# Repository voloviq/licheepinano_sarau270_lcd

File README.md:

# licheepinano_sarau270_lcd
LicheePi Nano Sara U270 Development Board

3D View of Board

PCB footprint is desinged for R19-2 SCI package

https://www.tme.eu/pl/details/absp-19/obudowy-uniwersalne/sci/r19-2/

### Limitation

GSM antenna is not well designed. In this pcb footprint it can be difficult or impossible to do it well. To achieve maximum performance use SMD connector with external antenna.

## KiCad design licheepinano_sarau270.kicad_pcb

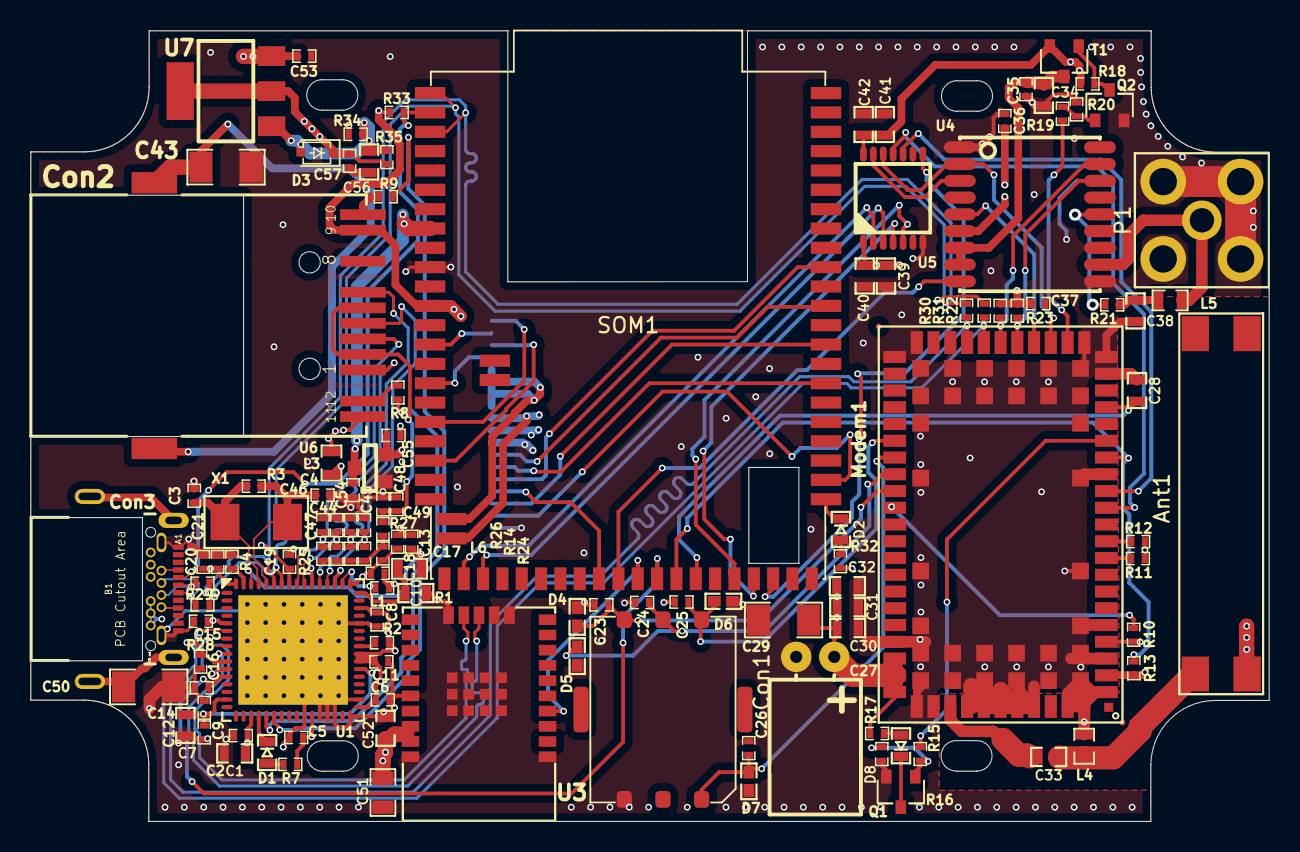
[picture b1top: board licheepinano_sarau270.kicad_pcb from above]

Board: 4 copper layers, 81.3 x 51.9 mm, 120 parts (1 on the bottom side), 92 nets.

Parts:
Ant1: MEE04
C1, C7: 4.7uF/6V3; 4_7uF_0603
C2, C5, C6, C8, C9, C11, C12, C13, C14, C15, C16, C17, C18, C19, C20, C21, C35, C36, C37: 100nF/50V; 100nF_0402
C3, C4: 30pF/50V; 30pF_0402
C10, C34, C38, C39, C41: 1uF/6V3; 1uF_0603
C23, C24, C25, C26: 47pF/50V; 47pF_0402
C27: 220uF/6V3; 220uF_6_3V_Polymer_Horizontal_fi8_len8mm
C28, C30, C31, C32, C40, C42: 100nF/50V; 100nF_0603
C29: 47uF/6V3; 47uF_1206
C33: 10pF; 10pF_0603
C43, C50: 1nF/2kV; 1nF_2kV_1206
C44, C45, C46, C47: 15pF/50V; 15pF_0402
C48, C49: 22nF/25V; 22nF_0402
C51: 10uF/16V; 10uF_0805
C52: 100nF/16V; 100nF_0603
C53, C54, C55, C57: 1uF/10V; 1uF_0402
C56: 10uF/10V; 10uF_10V_0603
Con1: SIM8050-6-0-14-01-A
Con2: WE-RJ45_7498011122AR
Con3: USB_C_Wurth_632723130112; USB_C_632723130112
D1, D2, D8: KPG-1608SURKC-T; LED_KPG-1608SURKC-T
D3: NSR0530H-D; NSR0530H-D_SOD323
D4, D5, D6, D7: PESD0402-140
DIS1: LiangHaoCai_Ili9341_spi
L1, L3: LCBA-601
L4, L5: 39nH; 39nH_0603
L6: BLM15HG601SN1D; BLM15HG601SN1D_0402
Modem1: Sara_U270
P1: RF2-03E-T-00-50-G
Q1, Q2: BC847B; BC847B_SOT23
R1: 12k/1%; 12k4_0402
R2, R10, R11, R12, R15, R19: 10k; 10k_0402
R3: 1M; 1M_0402
R4: 12k/1%; 12k_0402
R7, R8, R9, R17, R32: 470R; 470R_0402
R13, R18: 100k; 100k_0402
R14, R24, R25, R26: 49R9/1%; 49R9_0402
R16, R20, R33: 47k; 47k_0402
R21, R27: 10R; 10R_0402
R22, R23: 2k7; 2k7_0402
R28, R29, R30, R31: 0R; 0R_0402
R34: 1k5; 1k5_0402
R35: 3k3; 3k3_0402
SOM1: LicheePiNano
T1: FDN304P; FDN304P_SOT23
U1: LAN9514I
U3: LILY-W132; LILY_W132
U4: MAX-M8C; Max-M8C
U5: TXB0104; TXB0104_TSSOP14
U6: AP2127K-2.8TRG1; AP2127K-2.8TRG1_SOT23
U7: LM317DCYR; LM317DCYR_SOT223
X1: ABM3-25.000MHZ-D2Y-T

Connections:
3V3: C1.1, C2.1, C5.1, C6.1, C8.1, C11.1, C39.1, C40.1, C51.1, C52.1, Con2.9, Con2.11, L3.2, R2.2, R7.1, R32.1, R33.1, SOM1.53, U1.11, U1.19, U1.27, U1.33, U1.39, U1.40, U1.46, U3.8, U3.9, U5.1
/Ethernet Connector Module/LED_Green_-: Con2.12, R8.1
/Ethernet Connector Module/LED_Yellow_-: Con2.10, R9.1
/Ethernet Connector Module/POWER_IN_3V3: C15.1, C16.1, C17.1, C18.1, C19.1, C20.1, C21.1, L3.1, L6.1, U1.5, U1.10, U1.49, U1.51, U1.54, U1.57, U1.64
/Ethernet Connector Module/SHIELD1: C43.1, Con2.Z1, Con2.Z2
/GPS Module/1V8: C37.1, R22.2, R23.2
/GPS Module/GNSS_ENABLE: Modem1.23, R19.2
/GPS Module/GPS_EXTINT: Modem1.25, U4.5
/GPS Module/GPS_V_BCKP: C36.1, Modem1.2, R13.1, U4.6
/GPS Module/POWER_IN_1V8: C41.1, C42.1, Modem1.4, R10.2, R18.2, T1.S, U5.14
/LCD Module/CLK: DIS1.3, SOM1.14
/LCD Module/CS: DIS1.5, SOM1.10
/LCD Module/DC: DIS1.4, SOM1.34
/LCD Module/LED_A: DIS1.10, SOM1.65
/LCD Module/LED_K1: DIS1.11, DIS1.12, DIS1.13, DIS1.14, SOM1.66
/LCD Module/MISO: DIS1.7, SOM1.12
/LCD Module/MOSI: DIS1.6, SOM1.16
/LCD Module/POWER_IN_2V8: C55.1, DIS1.9, U6.2
/LicheePi Nano SOM/GPIO_PD0: Modem1.15, R13.2, SOM1.30
/LicheePi Nano SOM/GPIO_PD1: C28.1, Modem1.18, SOM1.29
/LicheePi Nano SOM/GPIO_PD5: SOM1.25, U5.8
/LicheePi Nano SOM/GPIO_PD9: SOM1.33, U4.9
/LicheePi Nano SOM/GPIO_PD11: C14.1, SOM1.31, U1.12
/LicheePi Nano SOM/GPIO_PD19: DIS1.2, SOM1.21
/LicheePi Nano SOM/POWER_IN_5V0: C53.1, C54.1, Con3.A4, Con3.A9, Con3.B4, Con3.B9, SOM1.57, U6.3, U7.3
/LicheePi Nano SOM/TPX1: DIS1.17, SOM1.51
/LicheePi Nano SOM/TPX2: DIS1.15, SOM1.49
/LicheePi Nano SOM/TPY1: DIS1.18, SOM1.47
/LicheePi Nano SOM/TPY2: DIS1.16, SOM1.45
/LicheePi Nano SOM/USB_D_N: R28.1, R31.2, SOM1.64, U1.58
/LicheePi Nano SOM/USB_D_P: R29.1, R30.2, SOM1.62, U1.59
/LicheePi Nano SOM/USB_ID: Con3.A5, Con3.B2, Con3.B3, Con3.B5, R33.2, SOM1.63
/Logic Voltage Shifter/SIG1_HIGH_PART: SOM1.41, U5.2
/Logic Voltage Shifter/SIG1_LOW_PART: U4.3, U5.13
/Logic Voltage Shifter/SIG2_HIGH_PART: SOM1.40, U5.3
/Logic Voltage Shifter/SIG2_LOW_PART: Modem1.24, U4.2, U5.12
/Logic Voltage Shifter/SIG3_HIGH_PART: SOM1.26, U5.4
/Logic Voltage Shifter/SIG3_LOW_PART: Modem1.12, U5.11
/Logic Voltage Shifter/SIG4_HIGH_PART: SOM1.27, U5.5
/Logic Voltage Shifter/SIG4_LOW_PART: Modem1.13, U5.10
/Modem 3G/GPS_I2C_1V8_SCL: Modem1.27, R22.1, U4.17
/Modem 3G/GPS_I2C_1V8_SDA: Modem1.26, R23.1, U4.16
/Modem 3G/MODEM_POWER_IN: C27.1, C29.1, C30.1, C31.1, C32.1, C57.1, D3.1, Modem1.51, Modem1.52, Modem1.53, R17.1, R35.1, U7.2, U7.4
/Modem 3G/SIM_CLK: C25.2, Con1.C3, D6.1, Modem1.38
/Modem 3G/SIM_DET: Modem1.42, R10.1
/Modem 3G/SIM_IO: C26.2, Con1.C7, D7.1, Modem1.39
/Modem 3G/SIM_RST: C24.2, Con1.C2, D5.1, Modem1.40
/Modem 3G/VSIM: C23.2, Con1.C1, D4.1, Modem1.41
/UBlox WiFi Lily W132/ENABLE: SOM1.32, U3.14
/USB Hub Module/ETHERNET_RXN: C44.1, Con2.6, R14.2, U1.53
/USB Hub Module/ETHERNET_RXP: C45.1, Con2.4, R24.2, U1.52
/USB Hub Module/ETHERNET_TXN: C46.1, Con2.3, R25.2, U1.56
/USB Hub Module/ETHERNET_TXP: C47.1, Con2.1, R26.2, U1.55
/USB Hub Module/USB_D4_OUT_N: Modem1.28, R31.1, U1.6
/USB Hub Module/USB_D4_OUT_P: Modem1.29, R30.1, U1.7
/USB Hub Module/USB_D5_OUT_N: U1.8, U3.24
/USB Hub Module/USB_D5_OUT_P: U1.9, U3.23
GND: Ant1.0, C1.2, C2.2, C3.2, C4.1, C5.2, C6.2, C7.2, C8.2, C9.2, C10.2, C11.2, C12.2, C13.2, C14.2, C15.2, C16.2, C17.2, C18.2, C19.2, C20.2, C21.2, C23.1, C24.1, C25.1, C26.1, C27.2, C28.2, C29.2, C30.2, C31.2, C32.2, C34.2, C35.2, C36.2, C37.2, C38.2, C39.2, C40.2, C41.2, C42.2, C43.2, C44.2, C45.2, C46.2, C47.2, C48.2, C49.2, C50.2, C51.2, C52.2, C53.2, C54.2, C55.2, C56.2, C57.2, Con1.C5, Con3.A1, Con3.A12, Con3.B1, Con3.B12, D4.2, D5.2, D6.2, D7.2, DIS1.1, DIS1.8, L4.2, Modem1.1, Modem1.3, Modem1.5, Modem1.14, Modem1.20, Modem1.21, Modem1.22, Modem1.30, Modem1.32, Modem1.33, Modem1.43, Modem1.50, Modem1.54, Modem1.55, Modem1.57, Modem1.58, Modem1.59, Modem1.60, Modem1.61, Modem1.63, Modem1.64, Modem1.65, Modem1.66, Modem1.67, Modem1.68, Modem1.69, Modem1.70, Modem1.71, Modem1.72, Modem1.73, Modem1.74, Modem1.75, Modem1.76, Modem1.77, Modem1.78, Modem1.79, Modem1.80, Modem1.81, Modem1.82, Modem1.83, Modem1.84, Modem1.85, Modem1.86, Modem1.87, Modem1.88, Modem1.89, Modem1.90, Modem1.91, Modem1.92, Modem1.93, Modem1.94, Modem1.95, Modem1.96, P1.2, Q1.2, Q2.2, R1.2, R4.1, R11.2, R12.2, R16.2, R20.2, R34.2, SOM1.55, U1.26, U1.28, U1.29, U1.30, U1.32, U1.34, U1.44, U1.65, U3.0, U3.6, U3.10, U3.11, U3.13, U3.21, U3.22, U3.25, U4.1, U4.10, U4.12, U5.7, U6.1
unnamed: Ant1.1, C33.1, L4.1
unnamed: C3.1, R3.1, U1.61, X1.2
unnamed: C4.2, R3.2, U1.60, X1.1
unnamed: C10.1, L1.2, U1.48
unnamed: C7.1, C9.1, C12.1, U1.15, U1.38
unnamed: C13.1, L1.1, U1.62
unnamed: C33.2, Modem1.56
unnamed: C34.1, C35.1, T1.D, U4.7, U4.8
unnamed: C38.1, L5.2, R21.1
unnamed: C48.1, C49.1, Con2.2, Con2.5, R27.2
unnamed: C50.1, Con3.S1, Con3.S2, Con3.S3, Con3.S4
unnamed: C56.1, D3.2, R34.1, R35.2, U7.1
unnamed: Con3.A6, Con3.B6, R29.2
unnamed: Con3.A7, Con3.B7, R28.2
unnamed: D1.1, R7.2
unnamed: D1.2, U1.20
unnamed: D2.1, R32.2
unnamed: D2.2, SOM1.22
unnamed: D8.1, R17.2
unnamed: D8.2, Q1.3
unnamed: L5.1, P1.1, U4.11
unnamed: L6.2, R14.1, R24.1, R25.1, R26.1, R27.1
unnamed: Modem1.9, R11.1
unnamed: Modem1.10, R12.1
unnamed: Modem1.16, R15.2
unnamed: Q1.1, R15.1, R16.1
unnamed: Q2.1, R19.1, R20.1
unnamed: Q2.3, R18.1, T1.G
unnamed: R1.1, U1.50
unnamed: R2.1, U1.41
unnamed: R4.2, U1.63
unnamed: R8.2, U1.21
unnamed: R9.2, U1.22
unnamed: R21.2, U4.14

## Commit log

2020-11-14 Initial
2020-11-15 Added Hub USB, Modem 3G and GPS
2020-11-21 Updated schematic
2020-11-21 Added logic level shifter on pcb
2020-11-22 Continue connections on schematic
2020-11-28 Added ethernet connector on pcb
2020-11-28 Added connection for ethernet modules
2020-11-28 Added WiFi and figurated some components on pcb
2020-11-28 Schematic finished, with check ERC
2020-11-28 Updated README.md and figurated components on pcb
2020-11-30 Added most of the pcb connections
2020-12-01 Added all connections, usb and ethernet track not aligned yet, component references not aligned, gerbers not generated
2020-12-01 Aligned all sillks and generated BOM, Gerbser, Schematic PDF
2020-12-01 Tuned high speed tracks
2020-12-02 Added package
2020-12-08 Rotate sim card holder
2021-01-03 Applied all issues
